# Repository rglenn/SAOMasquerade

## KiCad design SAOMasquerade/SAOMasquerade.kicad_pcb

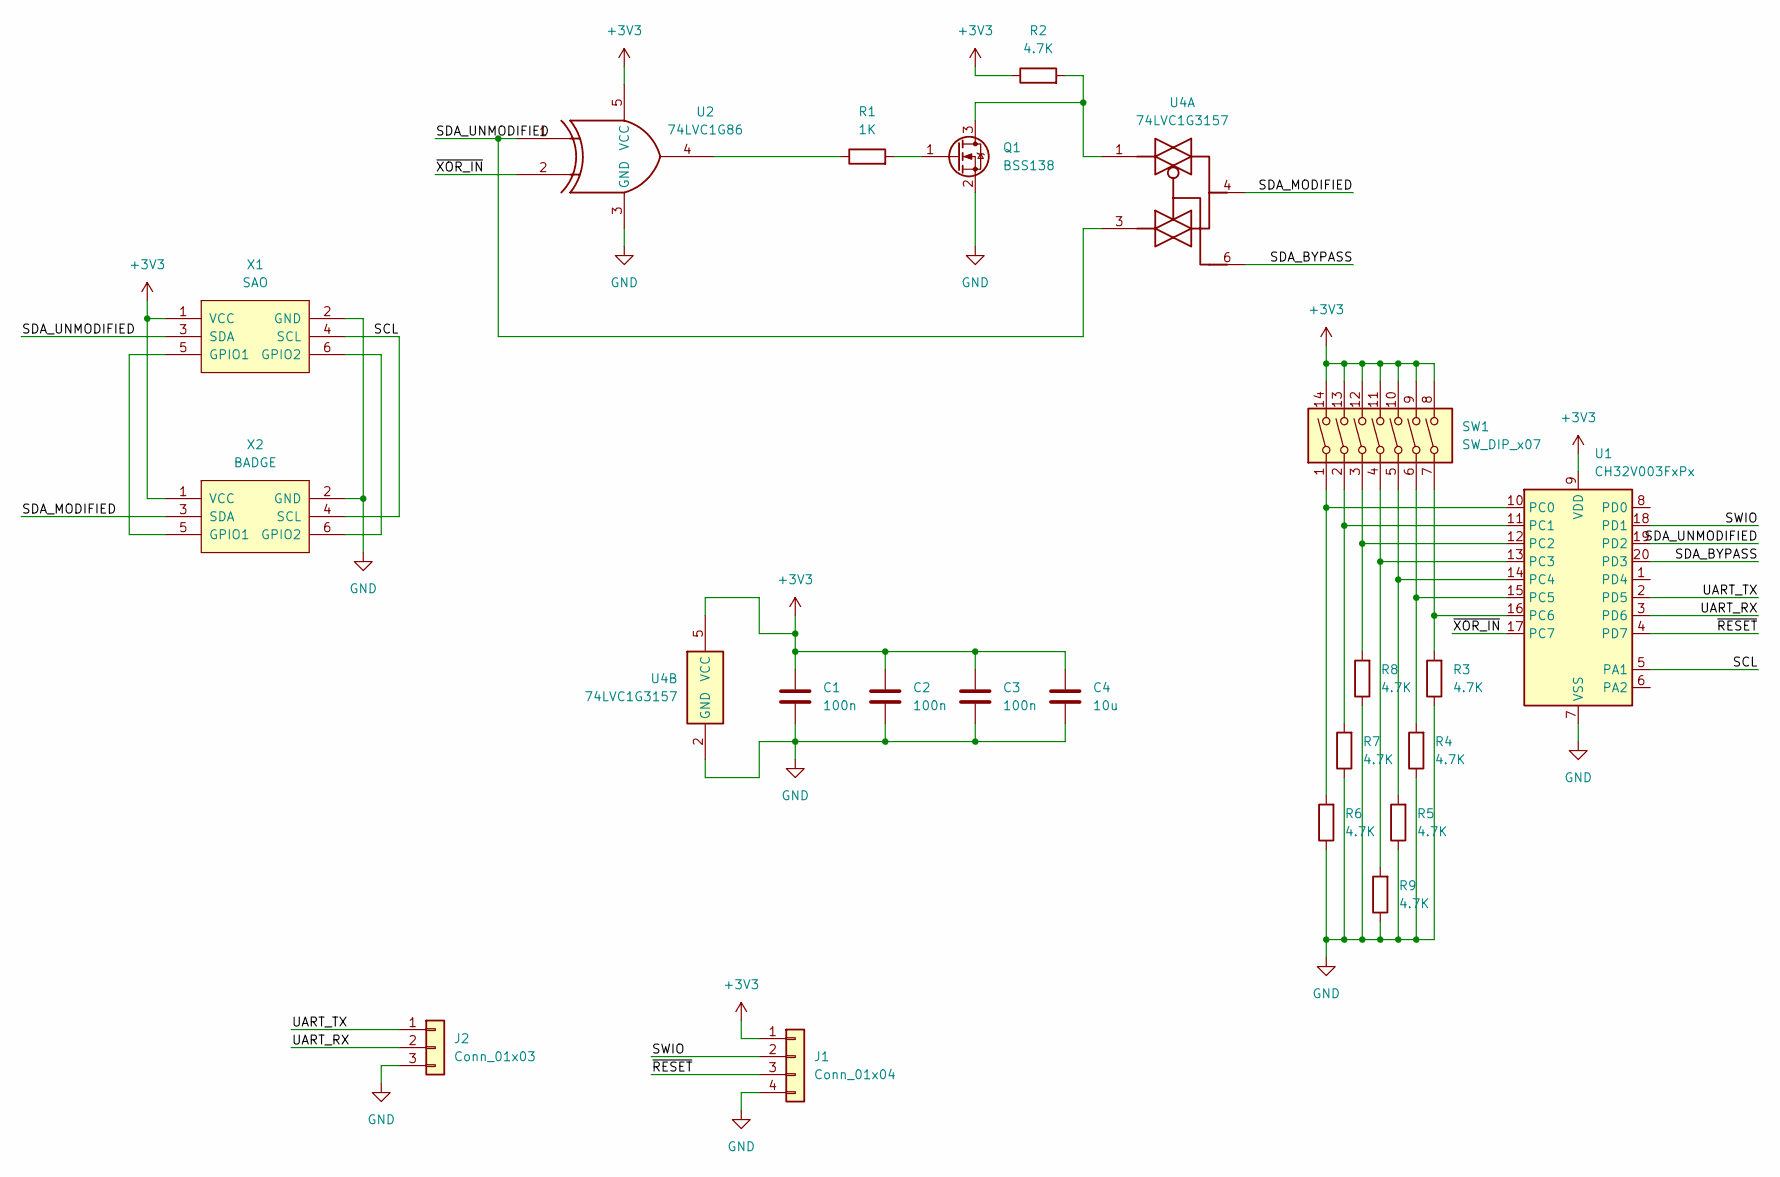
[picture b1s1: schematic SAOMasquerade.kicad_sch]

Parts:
C1, C2, C3: 100n; C_0603_1608Metric_Pad1.08x0.95mm_HandSolder
C4: 10u; C_0805_2012Metric_Pad1.18x1.45mm_HandSolder
J1: Conn_01x04; PinHeader_1x04_P2.54mm_Vertical
J2: Conn_01x03; PinHeader_1x03_P2.54mm_Vertical
Q1: BSS138; SOT-23_Handsoldering
R1: 1K; R_0603_1608Metric_Pad0.98x0.95mm_HandSolder
R2, R3, R4, R5, R6, R7, R8, R9: 4.7K; R_0603_1608Metric_Pad0.98x0.95mm_HandSolder
SW1: SW_DIP_x07; SW_DIP_SPSTx07_Slide_9.78x19.96mm_W7.62mm_P2.54mm
U1: CH32V003FxPx; TSSOP-20_4.4x6.5mm_P0.65mm
U2: 74LVC1G86; SOT-23-5_HandSoldering
U4: 74LVC1G3157; SOT-23-6_Handsoldering
X1: SAO; Simple_Addon_v2-SAO-2x3
X2: BADGE; Simple_Addon_v2-BADGE-2x3

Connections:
+3V3: C1.1, C2.1, C3.1, C4.1, J1.1, R2.1, SW1.8, SW1.9, SW1.10, SW1.11, SW1.12, SW1.13, SW1.14, U1.9 (VDD), U2.5 (VCC), U4.5 (VCC), X1.1 (VCC), X2.1 (VCC)
/SCL: U1.5 (PA1), X1.4 (SCL), X2.4 (SCL)
/SDA_BYPASS: U1.20 (PD3), U4.6
/SDA_MODIFIED: U4.4, X2.3 (SDA)
/SDA_UNMODIFIED: U1.19 (PD2), U2.1, U4.3, X1.3 (SDA)
/SWIO: J1.2, U1.18 (PD1)
/UART_RX: J2.2, U1.3 (PD6)
/UART_TX: J2.1, U1.2 (PD5)
/~RESET: J1.3, U1.4 (PD7)
/~XOR_IN: U1.17 (PC7), U2.2
GND: C1.2, C2.2, C3.2, C4.2, J1.4, J2.3, Q1.2 (S), R3.1, R4.1, R5.1, R6.1, R7.1, R8.1, R9.1, U1.7 (VSS), U2.3 (GND), U4.2 (GND), X1.2 (GND), X2.2 (GND)
unnamed: Q1.3 (D), R2.2, U4.1
unnamed: Q1.1 (G), R1.2
unnamed: R1.1, U2.4
unnamed: R6.2, SW1.1, U1.10 (PC0)
unnamed: R7.2, SW1.2, U1.11 (PC1)
unnamed: R8.2, SW1.3, U1.12 (PC2)
unnamed: R9.2, SW1.4, U1.13 (PC3)
unnamed: R5.2, SW1.5, U1.14 (PC4)
unnamed: R4.2, SW1.6, U1.15 (PC5)
unnamed: R3.2, SW1.7, U1.16 (PC6)
unnamed: X1.5 (GPIO1), X2.5 (GPIO1)
unnamed: X1.6 (GPIO2), X2.6 (GPIO2)

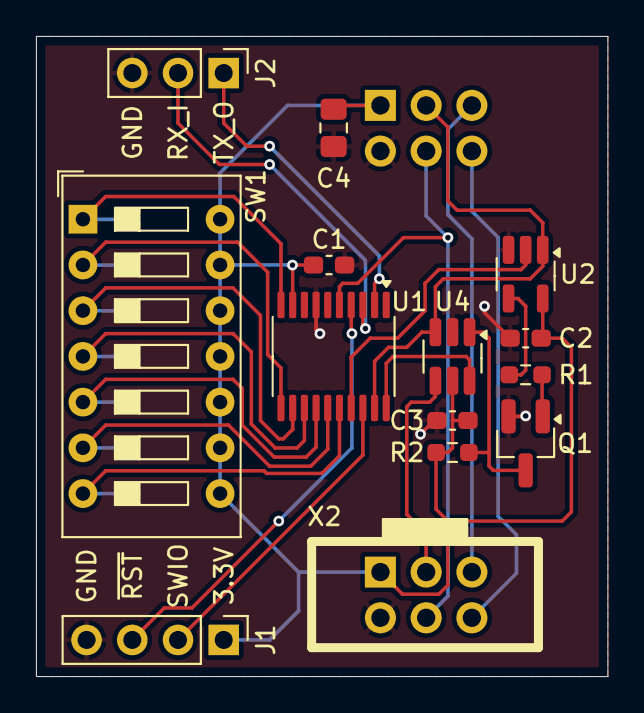
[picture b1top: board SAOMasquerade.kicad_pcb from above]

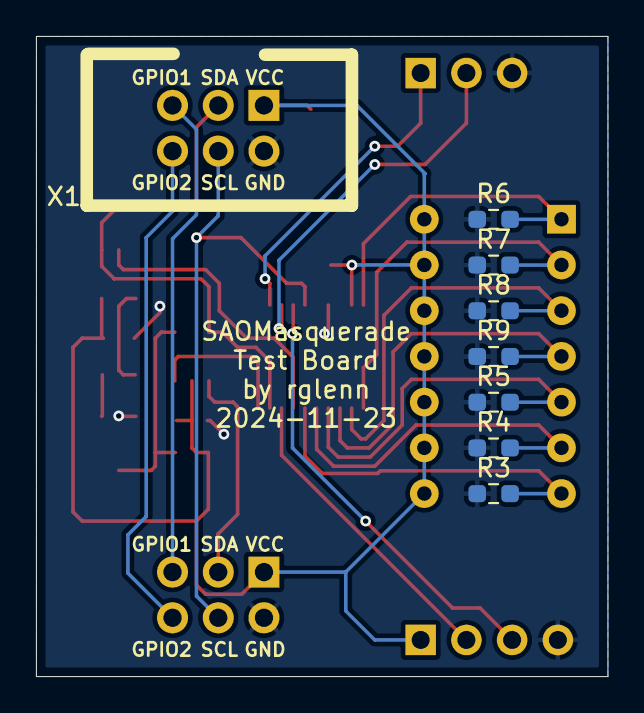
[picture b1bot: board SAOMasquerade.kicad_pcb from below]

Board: 2 copper layers, 31.8 x 35.6 mm, 22 parts (7 on the bottom side), 23 nets.

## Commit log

2024-11-23 Adding first schematic rev
2024-11-23 Updating schematic to use analog switch instead of open drain NAND
2024-11-23 Adding debuggability
